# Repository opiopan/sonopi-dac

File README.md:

Sonopi DAC
===

Sonopi DAC is a hat card for Raspberry Pi to add a audio line output capability.
This hat board is designed to adapt to both of formfactor, Raspbery pi model B+ and Raspberry pi Zero.<br>
[TI PCM5122](http://www.ti.com/product/PCM5122?keyMatch=PCM5122&tisearch=Search-EN-everything&usecase=part-number) is isntalled as DAC module, and Sonopi DAC design is compatible with [Hifiberry DAC+ Pro](https://www.hifiberry.com/shop/boards/hifiberry-dac-pro/) from Raspberry Pi point of view. It means that no special driver is necessary to use Sonopi DAC.

This hardware design is published under open source lincence. You can use and modify this design freely. There is also no limitation in commercial use.

## How to setup
Due to enable drivers for Sonopi DAC in Linux ALSA system, add a following line in ```/boot/config.txt```. Then rebooot a Raspberry Pi.

**Kernel Version $\lt$ 6.1.77 :**
```
dtoverlay=hifiberry-dacplus
```
**Kernel Version $\ge$ 6.1.77**
```
dtoverlay=hifiberry-dacplus-pro
```

## PCB Design
> [!NOTE]
> This PCB has been confirmed to work as intended.
> However, there has been a report of issues with a different artwork based on the schematic below. See [issue #1](https://github.com/opiopan/sonopi-dac/issues/1) for details.

## BOM List
Components               | Value / Product Number      | Remarks
-------------------------|-----------------------------|------------------------------
U1                       | PCM5122                     |
U2                       | MCP1703AT-3302E/CB          | 3.3V LDO
X1                       | 22.5792MHz Oscillator (3225)|
X2                       | 24.576MHz Oscillator (3225) |
R1, R2                   | 470Ω (1608)                 |
C1, C2                   | 1uF (1608)                  |
C3, C5, C7, C11          | 10uF/16V (3216)             |
C4, C6, C8, C12, C13, C14| 0.1uF/100V (1608)           |
C9, C10                  | 2.2uF/25V (2012)            |
C15, C16                 | 2.2nF/50V (1608)            |
J1                       | HLR-3201VXB-004HG           | RCA Jack (White)
J2                       | HLR-3201VXB-003HG           | RCA Jack (Red)

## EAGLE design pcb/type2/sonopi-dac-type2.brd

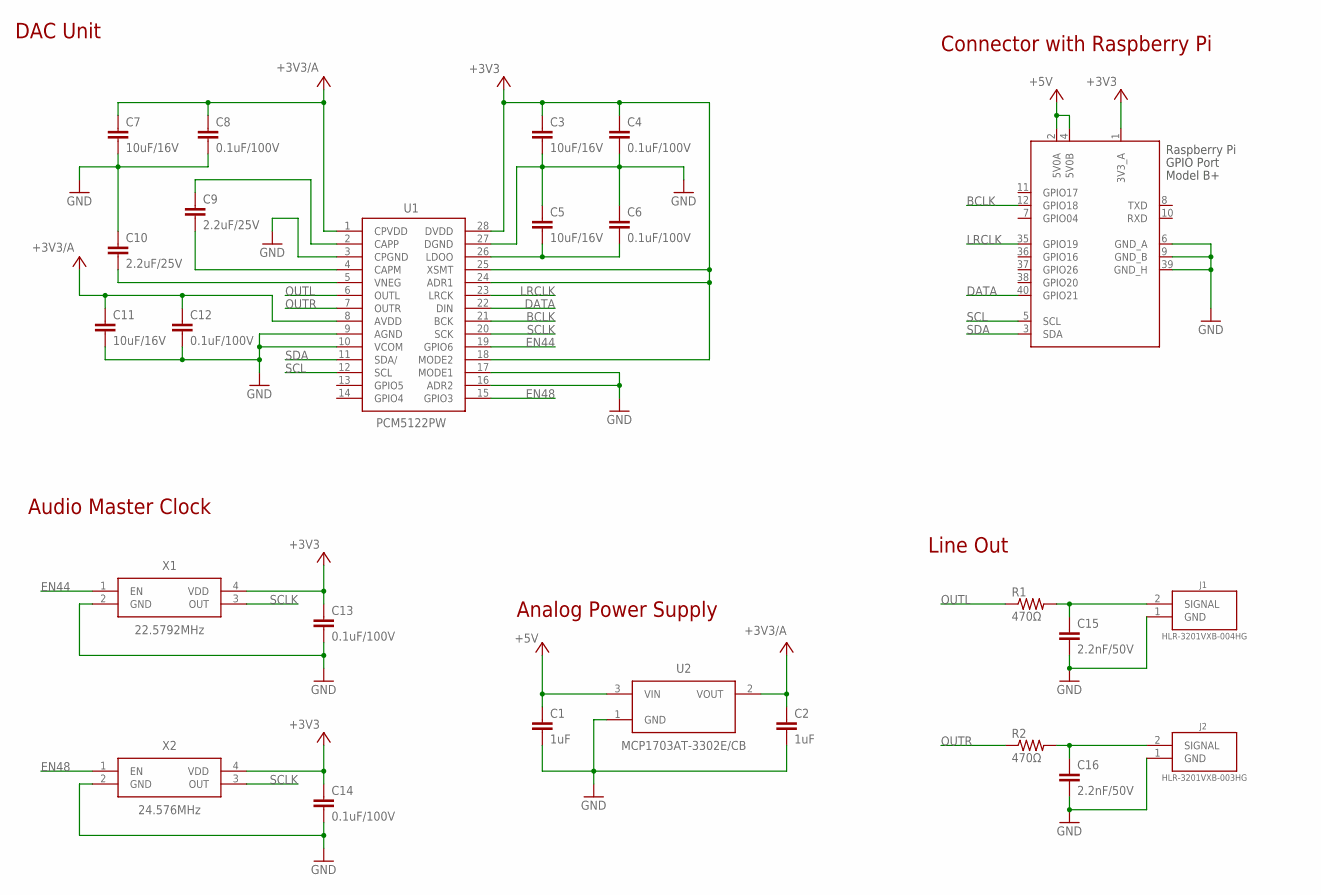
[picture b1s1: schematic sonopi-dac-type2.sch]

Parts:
C1, C2: 1uF; C0603
C3, C5, C7, C11: 10uF/16V; C3216
C4, C6, C8, C12, C13, C14: 0.1uF/100V; C0603
C9, C10: 2.2uF/25V; C0805
C15, C16: 2.2nF/50V; C0603
J1: HLR-3201VXB-004HG; HLR-3201VXB
J2: HLR-3201VXB-003HG; HLR-3201VXB
J3: RASPI_BOARD_B+#_ZERO; RASPI_BOARD_B+HAT_ZERO
R1, R2: 470Ω; R0603
U1: PCM5122PW; SOP65P640X120-28N
U2: MCP1703AT-3302E/CB; SOT23
X1: 22.5792MHz; 3225-SMD-HS
X2: 24.576MHz; 3225-SMD-HS

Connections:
+3V3: C3.1, C4.1, C13.1, C14.1, J3.1 (3V3_A), U1.18 (MODE2), U1.24 (ADR1), U1.25 (XSMT), U1.28 (DVDD), X1.4 (VDD), X2.4 (VDD)
+3V3/A: C2.1, C7.1, C8.1, C11.1, C12.1, U1.1 (CPVDD), U1.8 (AVDD), U2.2 (VOUT)
+5V: C1.1, J3.2 (5V0A), J3.4 (5V0B), U2.3 (VIN)
BCLK: J3.12 (GPIO18), U1.21 (BCK)
CAPM: C9.2, U1.4 (CAPM)
CAPP: C9.1, U1.2 (CAPP)
DATA: J3.40 (GPIO21), U1.22 (DIN)
EN44: U1.19 (GPIO6), X1.1 (EN)
EN48: U1.15 (GPIO3), X2.1 (EN)
GND: C1.2, C2.2, C3.2, C4.2, C5.1, C6.1, C7.2, C8.2, C10.1, C11.2, C12.2, C13.2, C14.2, C15.2, C16.2, J1.1 (GND), J2.1 (GND), J3.6 (GND_A), J3.9 (GND_B), J3.39 (GND_H), U1.3 (CPGND), U1.9 (AGND), U1.10 (VCOM), U1.16 (ADR2), U1.17 (MODE1), U1.27 (DGND), U2.1 (GND), X1.2 (GND), X2.2 (GND)
LCH: C15.1, J1.2 (SIGNAL), R1.2
LDOO: C5.2, C6.2, U1.26 (LDOO)
LRCLK: J3.35 (GPIO19), U1.23 (LRCK)
OUTL: R1.1, U1.6 (OUTL)
OUTR: R2.1, U1.7 (OUTR)
RCH: C16.1, J2.2 (SIGNAL), R2.2
SCL: J3.5 (SCL), U1.12 (SCL)
SCLK: U1.20 (SCK), X1.3 (OUT), X2.3 (OUT)
SDA: J3.3 (SDA), U1.11 (SDA/)
VNEG: C10.2, U1.5 (VNEG)

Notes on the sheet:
Analog Power Supply
Connector with Raspberry Pi
DAC Unit
Audio Master Clock
Line Out

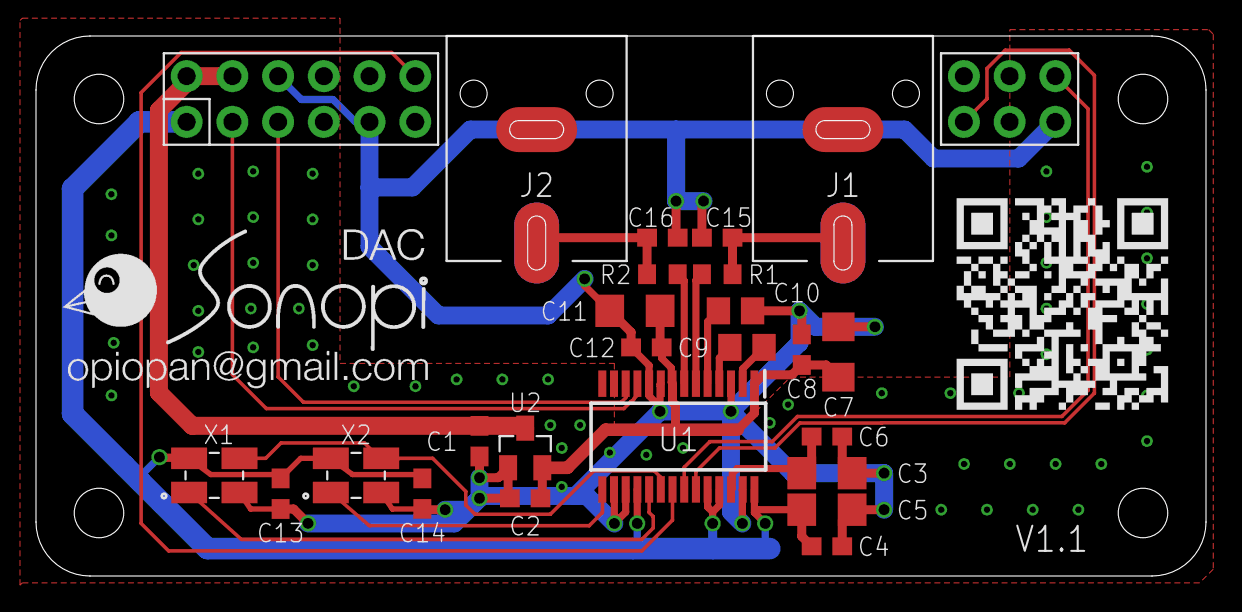
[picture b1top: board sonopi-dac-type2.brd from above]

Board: 2 copper layers, 65.0 x 30.0 mm, 27 parts (0 on the bottom side), 20 nets.

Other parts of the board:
U$1: SONOPI-DAC-LOGO
U$2: SONOPI-DAC-QRCODE

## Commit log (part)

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2019-11-17 initial commit, PCB schema design done
2019-11-17 fix a minor bug in schema
2019-11-18 fix a bug that a part of coupling capaciter does not be utilized
2019-11-18 initial artwork done
2019-11-21 add artwork design
2019-11-24 fix minor probrems, and add scripts to generate decal image for 3D rendering
2019-11-29 modify helper scripts
2019-11-30 add another desing that Linkman RCA jack is installed
2019-12-01 add BOM list
2019-12-30 add panelizing script
2019-12-30 add some files for panelizing
2020-06-13 change footprint of 3225 oscillator
2026-04-06 Address issue #2
2026-04-08 Address issue #1
2026-04-08 Update the README
